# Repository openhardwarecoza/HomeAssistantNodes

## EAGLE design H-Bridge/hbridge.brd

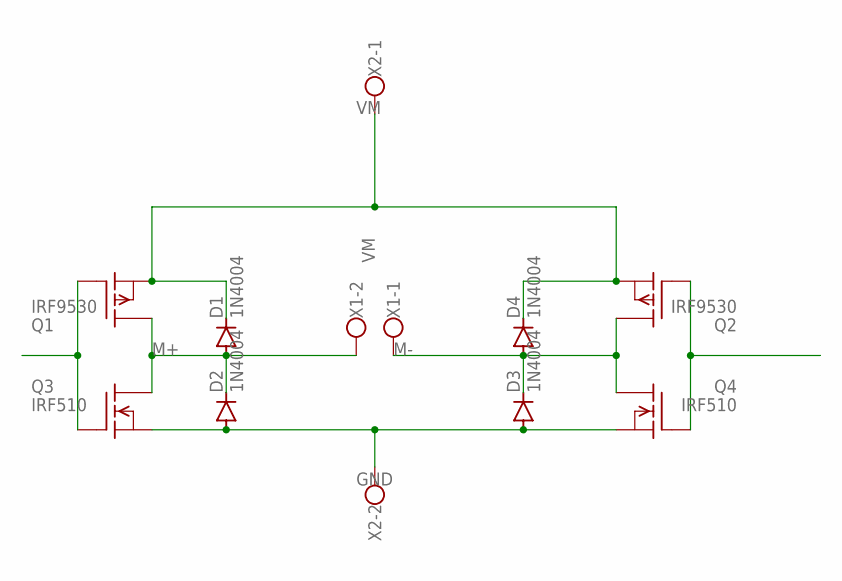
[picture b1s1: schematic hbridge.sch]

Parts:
D1, D2, D3, D4: 1N4004; DO41-10
Q1, Q2: IRF9530; TO220
Q3, Q4: IRF510; TO220
X1, X2: W237-102

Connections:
GND: D2.A, D3.A, Q3.3 (S), Q4.3 (S), X2.2
M+: D1.A, D2.C, Q1.2 (D), Q3.2 (D), X1.2
M-: D3.C, D4.A, Q2.2 (D), Q4.2 (D), X1.1
unnamed: Q1.1 (G), Q3.1 (G)
unnamed: Q2.1 (G), Q4.1 (G)
VM: D1.C, D4.C, Q1.3 (S), Q2.3 (S), X2.1

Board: 2 copper layers, 10 parts (0 on the bottom side), 6 nets, no tracks yet.

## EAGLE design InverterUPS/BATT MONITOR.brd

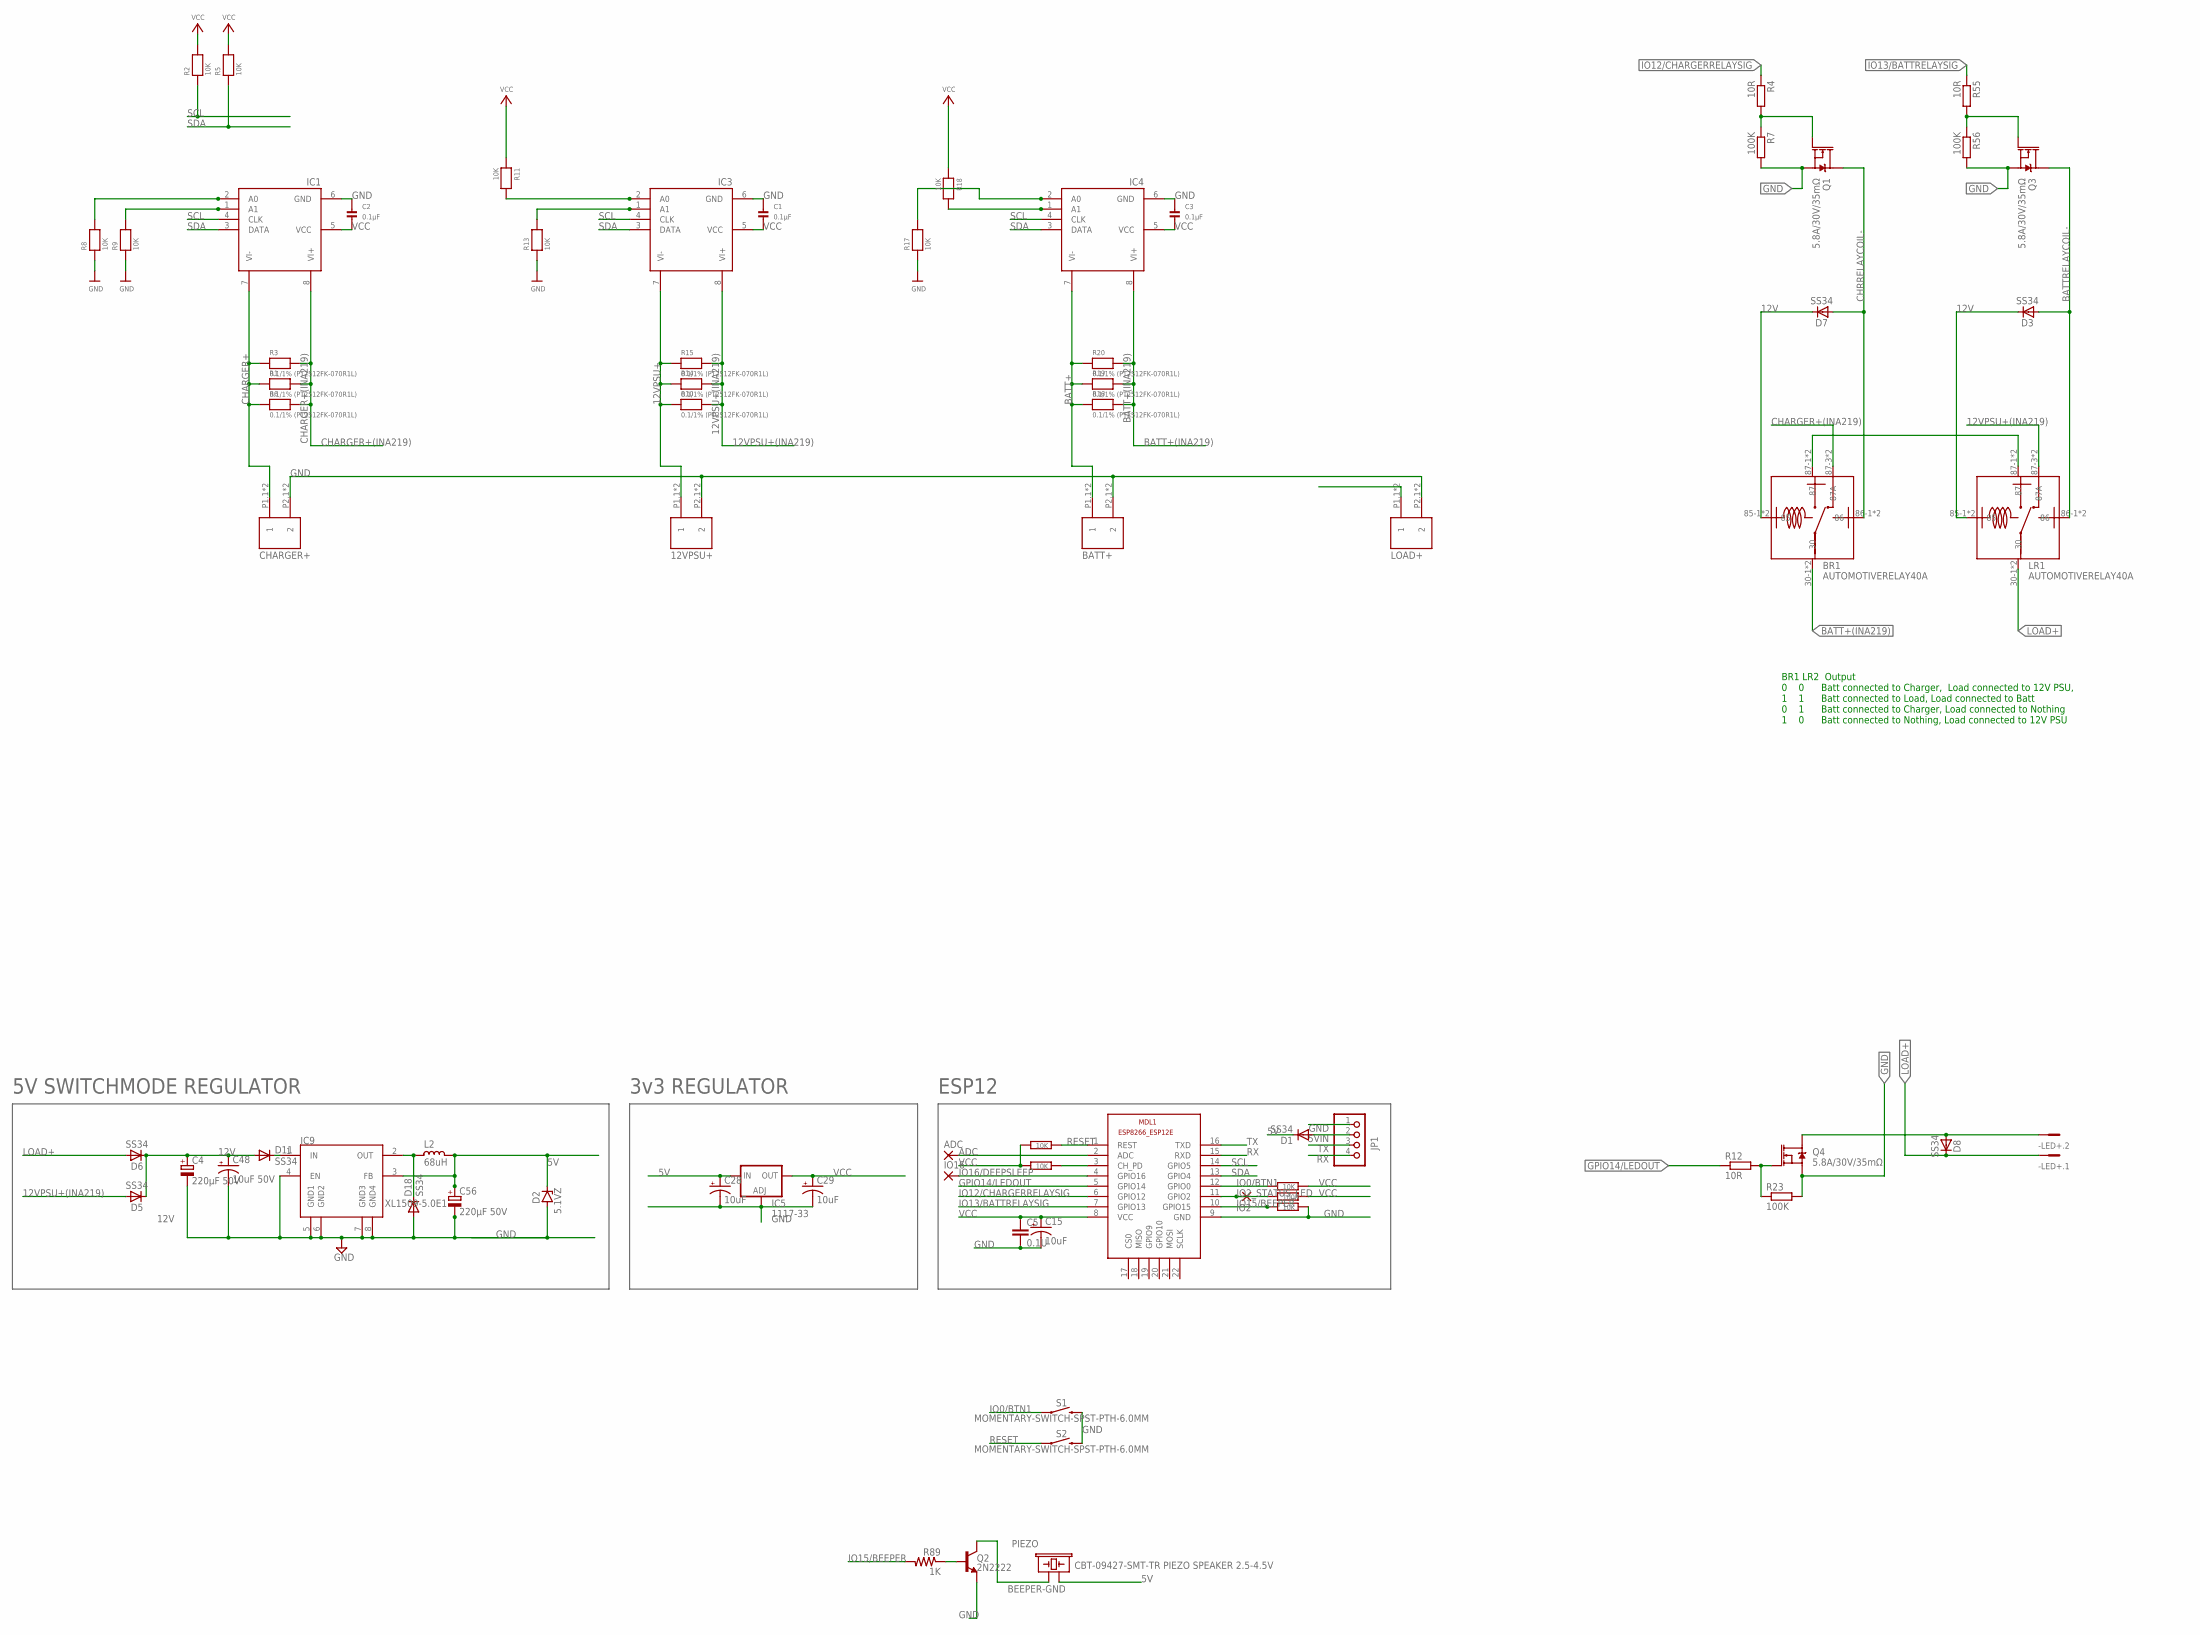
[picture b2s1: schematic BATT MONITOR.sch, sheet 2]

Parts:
-LED+: MCV2
ADC: 2,54/1,1
BR1: AUTOMOTIVERELAY40A
C1, C2, C3: 0.1µF; 1206
C4, C56: 220µF 50V; E3,5-10
C5: 0.1U; C1206
C15, C28, C29: 10uF; EIA3216
C48: 10uF 50V; EIA3216
CHARGER1, CHARGER2, CHARGER3, CHARGER4: BARRIERTERMINAL
D1, D11, D18: SS34; DO-214AC
D2: 5.1VZ; SMB
D3, D5, D6, D7, D8: SS34; SOD87
IC1, IC3, IC4: INA219D; SO08
IC5: 1117-33; SOT223
IC9: XL1509-5.0E1; SO08
IO2, IO16: 2,54/1,1
JP1: PINHD-1X4; 1X04
L2: 68uH; CD75
LR1: AUTOMOTIVERELAY40A
MDL1: ESP8266-12EESP8266-ESP12E; ESP8266-ESP12E
PIEZO: CBT-09427-SMT-TR PIEZO SPEAKER 2.5-4.5V; BUZZER-12MM
Q1, Q3, Q4: 5.8A/30V/35mΩ; SOT23-3
Q2: 2N2222; SOT23-3
R1, R3, R6, R10, R14, R15, R16, R19, R20: 0.1/1% (PT2512FK-070R1L); 2512
R2, R5, R8, R9, R11, R13, R17, R18: 10K; 1206
R4, R55: 10R; R1206
R7, R21, R56: 100K; R1206
R12: 10R; M1206
R22, R28, R29, R31: 10K; R1206
R23: 100K; M1206
R89: 1K; R1206
S1, S2: MOMENTARY-SWITCH-SPST-PTH-6.0MM; TACTILE_SWITCH_PTH_6.0MM

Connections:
5V: C28.A (+), C56.+, D1.1 (C), D2.C, IC5.3 (IN), IC9.3 (FB), L2.1, PIEZO.+ (1)
5VIN: D1.2 (A), JP1.2
12V: BR1.85-1 (85), BR1.85-2 (85), C4.+, C48.A (+), D3.1 (C), D5.1 (C), D6.1 (C), D7.1 (C), D11.2 (A), LR1.85-1 (85), LR1.85-2 (85)
12VPSU+: CHARGER4.P1.1 (1), CHARGER4.P1.2 (1), IC3.7 (VI-), R10.1, R14.1, R15.1
12VPSU+(INA219): D5.2 (A), IC3.8 (VI+), LR1.87-3 (87A), LR1.87-4 (87A), R10.2, R14.2, R15.2
ADC: ADC.1, MDL1.2 (ADC)
BATT+: CHARGER1.P1.1 (1), CHARGER1.P1.2 (1), IC4.7 (VI-), R16.1, R19.1, R20.1
BATT+(INA219): BR1.30-1 (30), BR1.30-2 (30), IC4.8 (VI+), R16.2, R19.2, R20.2
BATTRELAYCOIL-: D3.2 (A), LR1.86-1 (86), LR1.86-2 (86), Q3.3 (D)
BEEPER-GND: PIEZO.- (2), Q2.3 (C)
CHARGER+: CHARGER3.P1.1 (1), CHARGER3.P1.2 (1), IC1.7 (VI-), R1.1, R3.1, R6.1
CHARGER+(INA219): BR1.87-3 (87A), BR1.87-4 (87A), IC1.8 (VI+), R1.2, R3.2, R6.2
CHRRELAYCOIL-: BR1.86-1 (86), BR1.86-2 (86), D7.2 (A), Q1.3 (D)
GND: C1.1, C2.1, C3.1, C4.-, C5.2, C15.C (-), C28.C (-), C29.C (-), C48.C (-), C56.-, CHARGER1.P2.1 (2), CHARGER1.P2.2 (2), CHARGER2.P2.1 (2), CHARGER2.P2.2 (2), CHARGER3.P2.1 (2), CHARGER3.P2.2 (2), CHARGER4.P2.1 (2), CHARGER4.P2.2 (2), D2.A, D18.2 (A), IC1.6 (GND), IC3.6 (GND), IC4.6 (GND), IC5.1 (ADJ), IC9.4 (EN), IC9.5 (GND1), IC9.6 (GND2), IC9.7 (GND3), IC9.8 (GND4), JP1.1, MDL1.9 (GND), Q1.2 (S), Q2.2 (E), Q3.2 (S), Q4.2 (S), R7.2, R8.1, R9.1, R13.1, R17.1, R23.2, R31.2, R56.2, S1.3 (2), S2.3 (2)
GPIO14/LEDOUT: MDL1.5 (GPIO14), R12.1
IO0/BTN1: MDL1.12 (GPIO0), R22.1, S1.1
IO2_STATUS_LED: IO2.1, MDL1.11 (GPIO2), R21.1
IO12/CHARGERRELAYSIG: MDL1.6 (GPIO12), R4.1
IO13/BATTRELAYSIG: MDL1.7 (GPIO13), R55.1
IO15/BEEPER: MDL1.10 (GPIO15), R31.1, R89.2
IO16/DEEPSLEEP: IO16.1, MDL1.4 (GPIO16)
LOAD+: -LED+.1, CHARGER2.P1.1 (1), CHARGER2.P1.2 (1), D6.2 (A), D8.1 (C), LR1.30-1 (30), LR1.30-2 (30)
unnamed: D18.1 (C), IC9.2 (OUT), L2.2
unnamed: Q4.1 (G), R12.2, R23.1
unnamed: IC1.1 (A1), R9.2
unnamed: IC1.2 (A0), R8.2
unnamed: Q1.1 (G), R4.2, R7.1
unnamed: BR1.87-1 (87), BR1.87-2 (87), LR1.87-1 (87), LR1.87-2 (87)
unnamed: Q2.1 (B), R89.1
unnamed: IC3.1 (A1), R13.2
unnamed: IC3.2 (A0), R11.2
unnamed: IC4.1 (A1), R18.2
unnamed: IC4.2 (A0), R17.2
unnamed: MDL1.3 (CH_PD), R28.2
unnamed: D11.1 (C), IC9.1 (IN)
unnamed: Q3.1 (G), R55.2, R56.1
unnamed: -LED+.2, D8.2 (A), Q4.3 (D)
RESET: MDL1.1 (REST), R29.2, S2.1
RX: JP1.4, MDL1.15 (RXD)
SCL: IC1.4 (CLK), IC3.4 (CLK), IC4.4 (CLK), MDL1.14 (GPIO5), R2.1
SDA: IC1.3 (DATA), IC3.3 (DATA), IC4.3 (DATA), MDL1.13 (GPIO4), R5.1
TX: JP1.3, MDL1.16 (TXD)
VCC: C1.2, C2.2, C3.2, C5.1, C15.A (+), C29.A (+), IC1.5 (VCC), IC3.5 (VCC), IC4.5 (VCC), IC5.4 (OUT), MDL1.8 (VCC), R2.2, R5.2, R11.1, R18.1, R21.2, R22.2, R28.1, R29.1

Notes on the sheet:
BR1 LR2 Output 0 0 Batt connected to Charger, Load connected to 12V PSU, 1 1 Batt connected to Load, Load connected to Batt 0 1 Batt connected to Charger, Load connected to Nothing 1 0 Batt connected to Nothing, Load connected to 12V PSU
5V SWITCHMODE REGULATOR
3v3 REGULATOR
ESP12

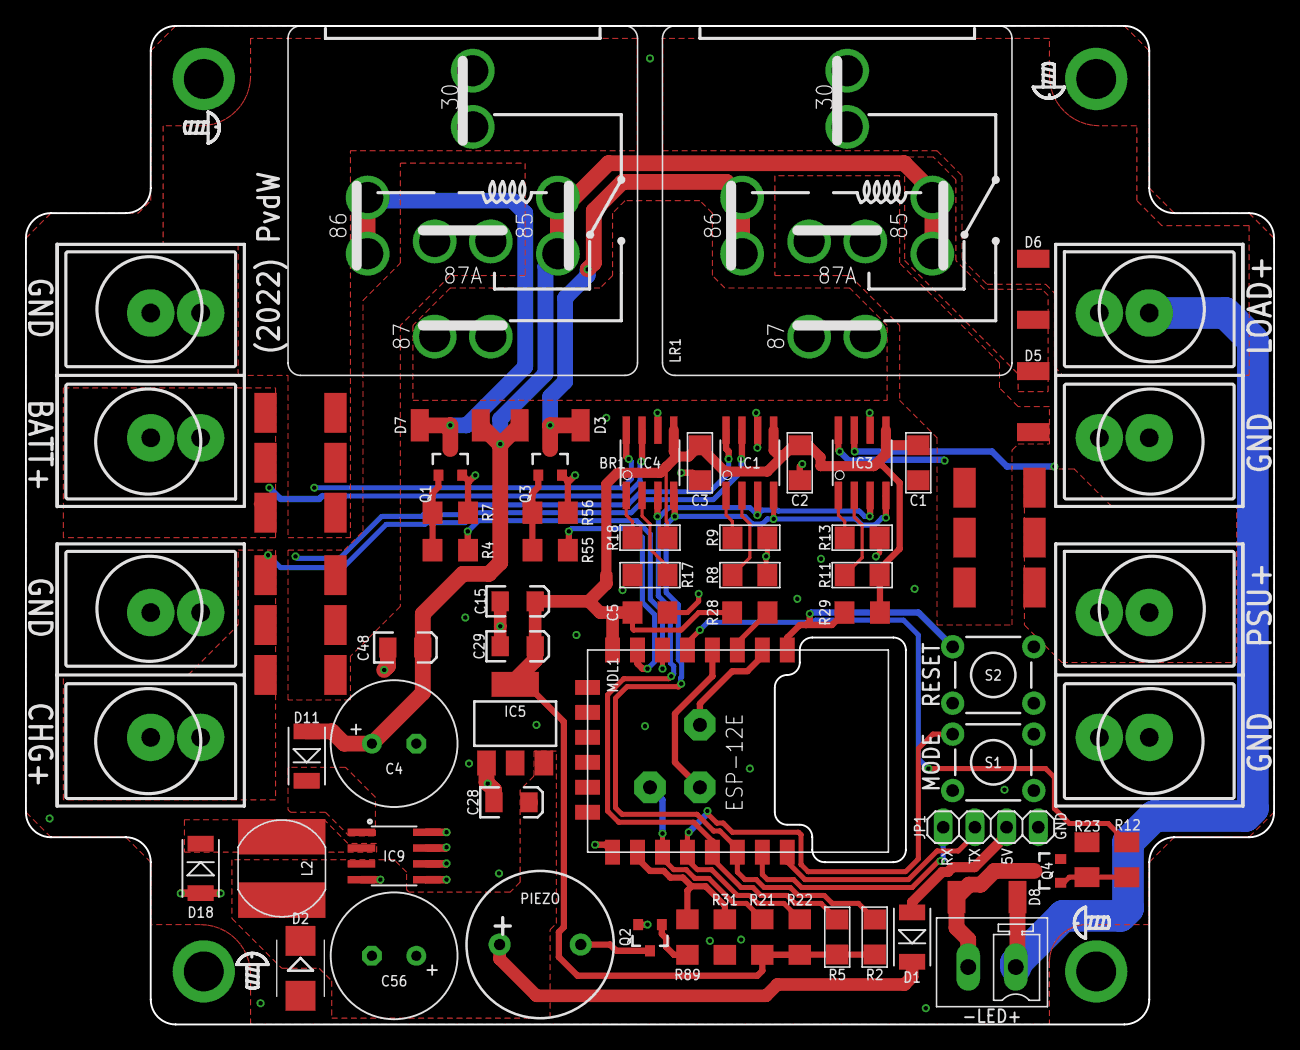
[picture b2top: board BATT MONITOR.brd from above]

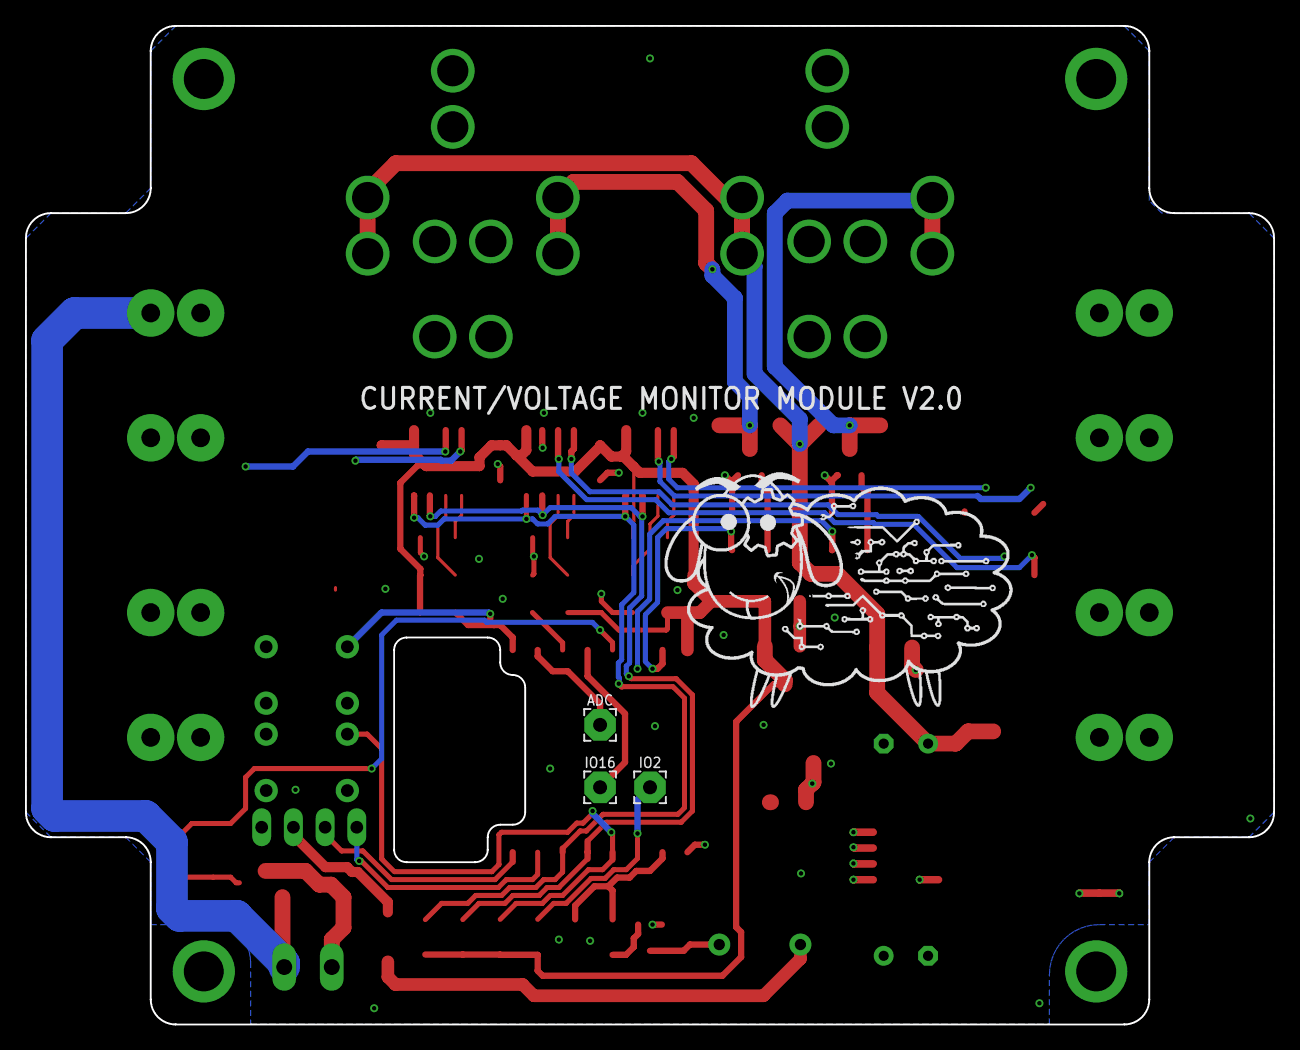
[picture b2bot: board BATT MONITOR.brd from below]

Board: 2 copper layers, 100.0 x 80.0 mm, 73 parts (3 on the bottom side), 43 nets.

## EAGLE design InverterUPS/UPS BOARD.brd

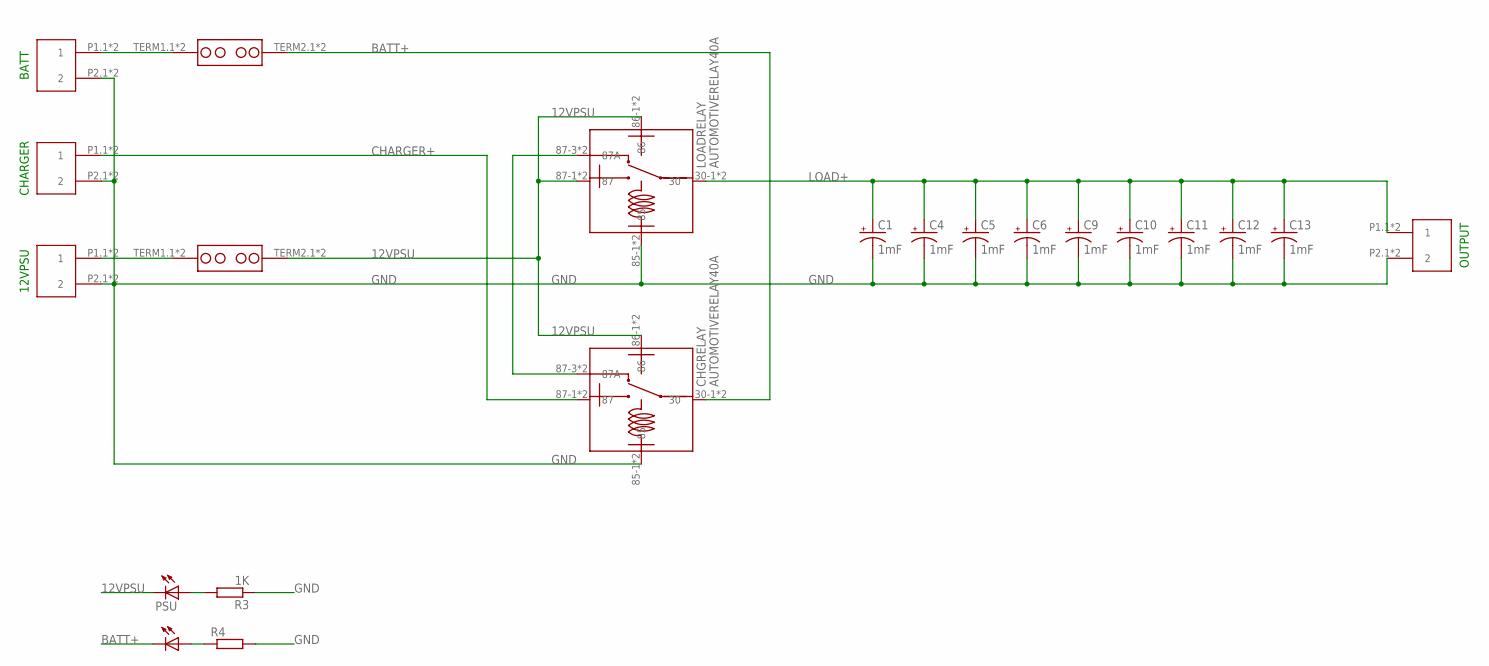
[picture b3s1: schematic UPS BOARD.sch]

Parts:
BATT: LED5MM
C1, C4, C5, C6, C9, C10, C11, C12, C13: 1mF; CPOL-RADIAL-5MM-10MM
CHARGER2, CHARGER3, CHARGER4, CHARGER5: BARRIERTERMINAL
CHGRELAY: AUTOMOTIVERELAY40A
LOADRELAY: AUTOMOTIVERELAY40A
PSU: LED5MM
R3, R4: 1K; 0204/7
U$15, U$17: ATQ-FUSE

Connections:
12VPSU: CHGRELAY.86-1 (86), CHGRELAY.86-2 (86), LOADRELAY.86-1 (86), LOADRELAY.86-2 (86), LOADRELAY.87-1 (87), LOADRELAY.87-2 (87), PSU.K (C), U$17.TERM2.1, U$17.TERM2.2
BATT+: BATT.K (C), CHGRELAY.30-1 (30), CHGRELAY.30-2 (30), U$15.TERM2.1, U$15.TERM2.2
CHARGER+: CHARGER5.P1.1 (1), CHARGER5.P1.2 (1), CHGRELAY.87-1 (87), CHGRELAY.87-2 (87)
GND: C1.-, C4.-, C5.-, C6.-, C9.-, C10.-, C11.-, C12.-, C13.-, CHARGER2.P2.1 (2), CHARGER2.P2.2 (2), CHARGER3.P2.1 (2), CHARGER3.P2.2 (2), CHARGER4.P2.1 (2), CHARGER4.P2.2 (2), CHARGER5.P2.1 (2), CHARGER5.P2.2 (2), CHGRELAY.85-1 (85), CHGRELAY.85-2 (85), LOADRELAY.85-1 (85), LOADRELAY.85-2 (85), R3.1, R4.2
LOAD+: C1.+, C4.+, C5.+, C6.+, C9.+, C10.+, C11.+, C12.+, C13.+, CHARGER4.P1.1 (1), CHARGER4.P1.2 (1), LOADRELAY.30-1 (30), LOADRELAY.30-2 (30)
unnamed: PSU.A, R3.2
unnamed: BATT.A, R4.1
unnamed: CHARGER3.P1.1 (1), CHARGER3.P1.2 (1), U$17.TERM1.1, U$17.TERM1.2
unnamed: CHGRELAY.87-3 (87A), CHGRELAY.87-4 (87A), LOADRELAY.87-3 (87A), LOADRELAY.87-4 (87A)
unnamed: CHARGER2.P1.1 (1), CHARGER2.P1.2 (1), U$15.TERM1.1, U$15.TERM1.2

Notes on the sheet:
CHARGER
12VPSU
OUTPUT
BATT

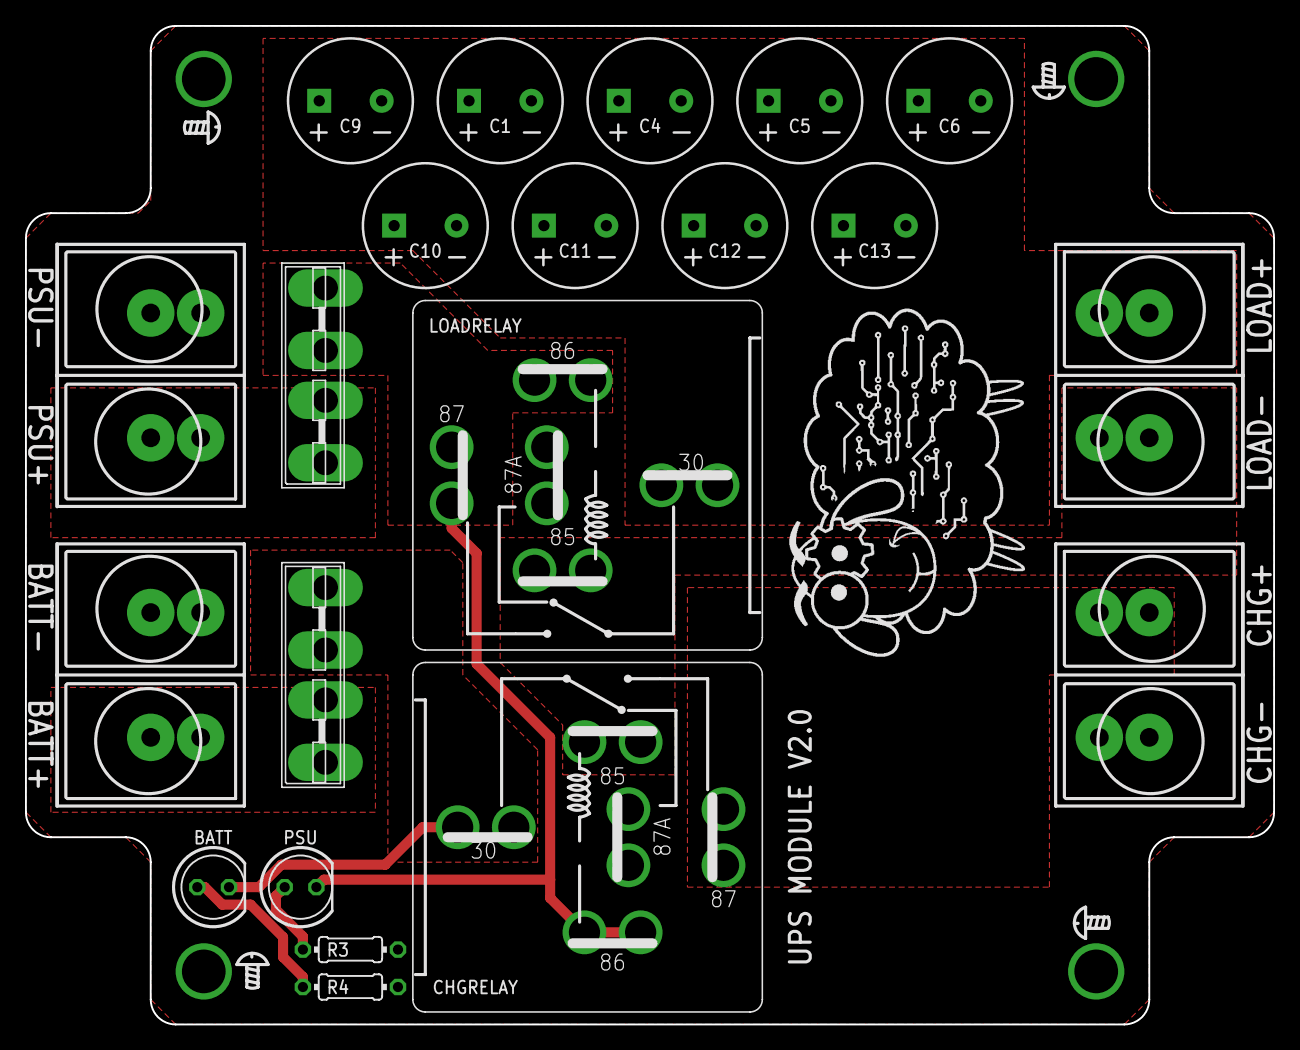
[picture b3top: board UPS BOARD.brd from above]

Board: 2 copper layers, 100.0 x 80.0 mm, 21 parts (0 on the bottom side), 10 nets.

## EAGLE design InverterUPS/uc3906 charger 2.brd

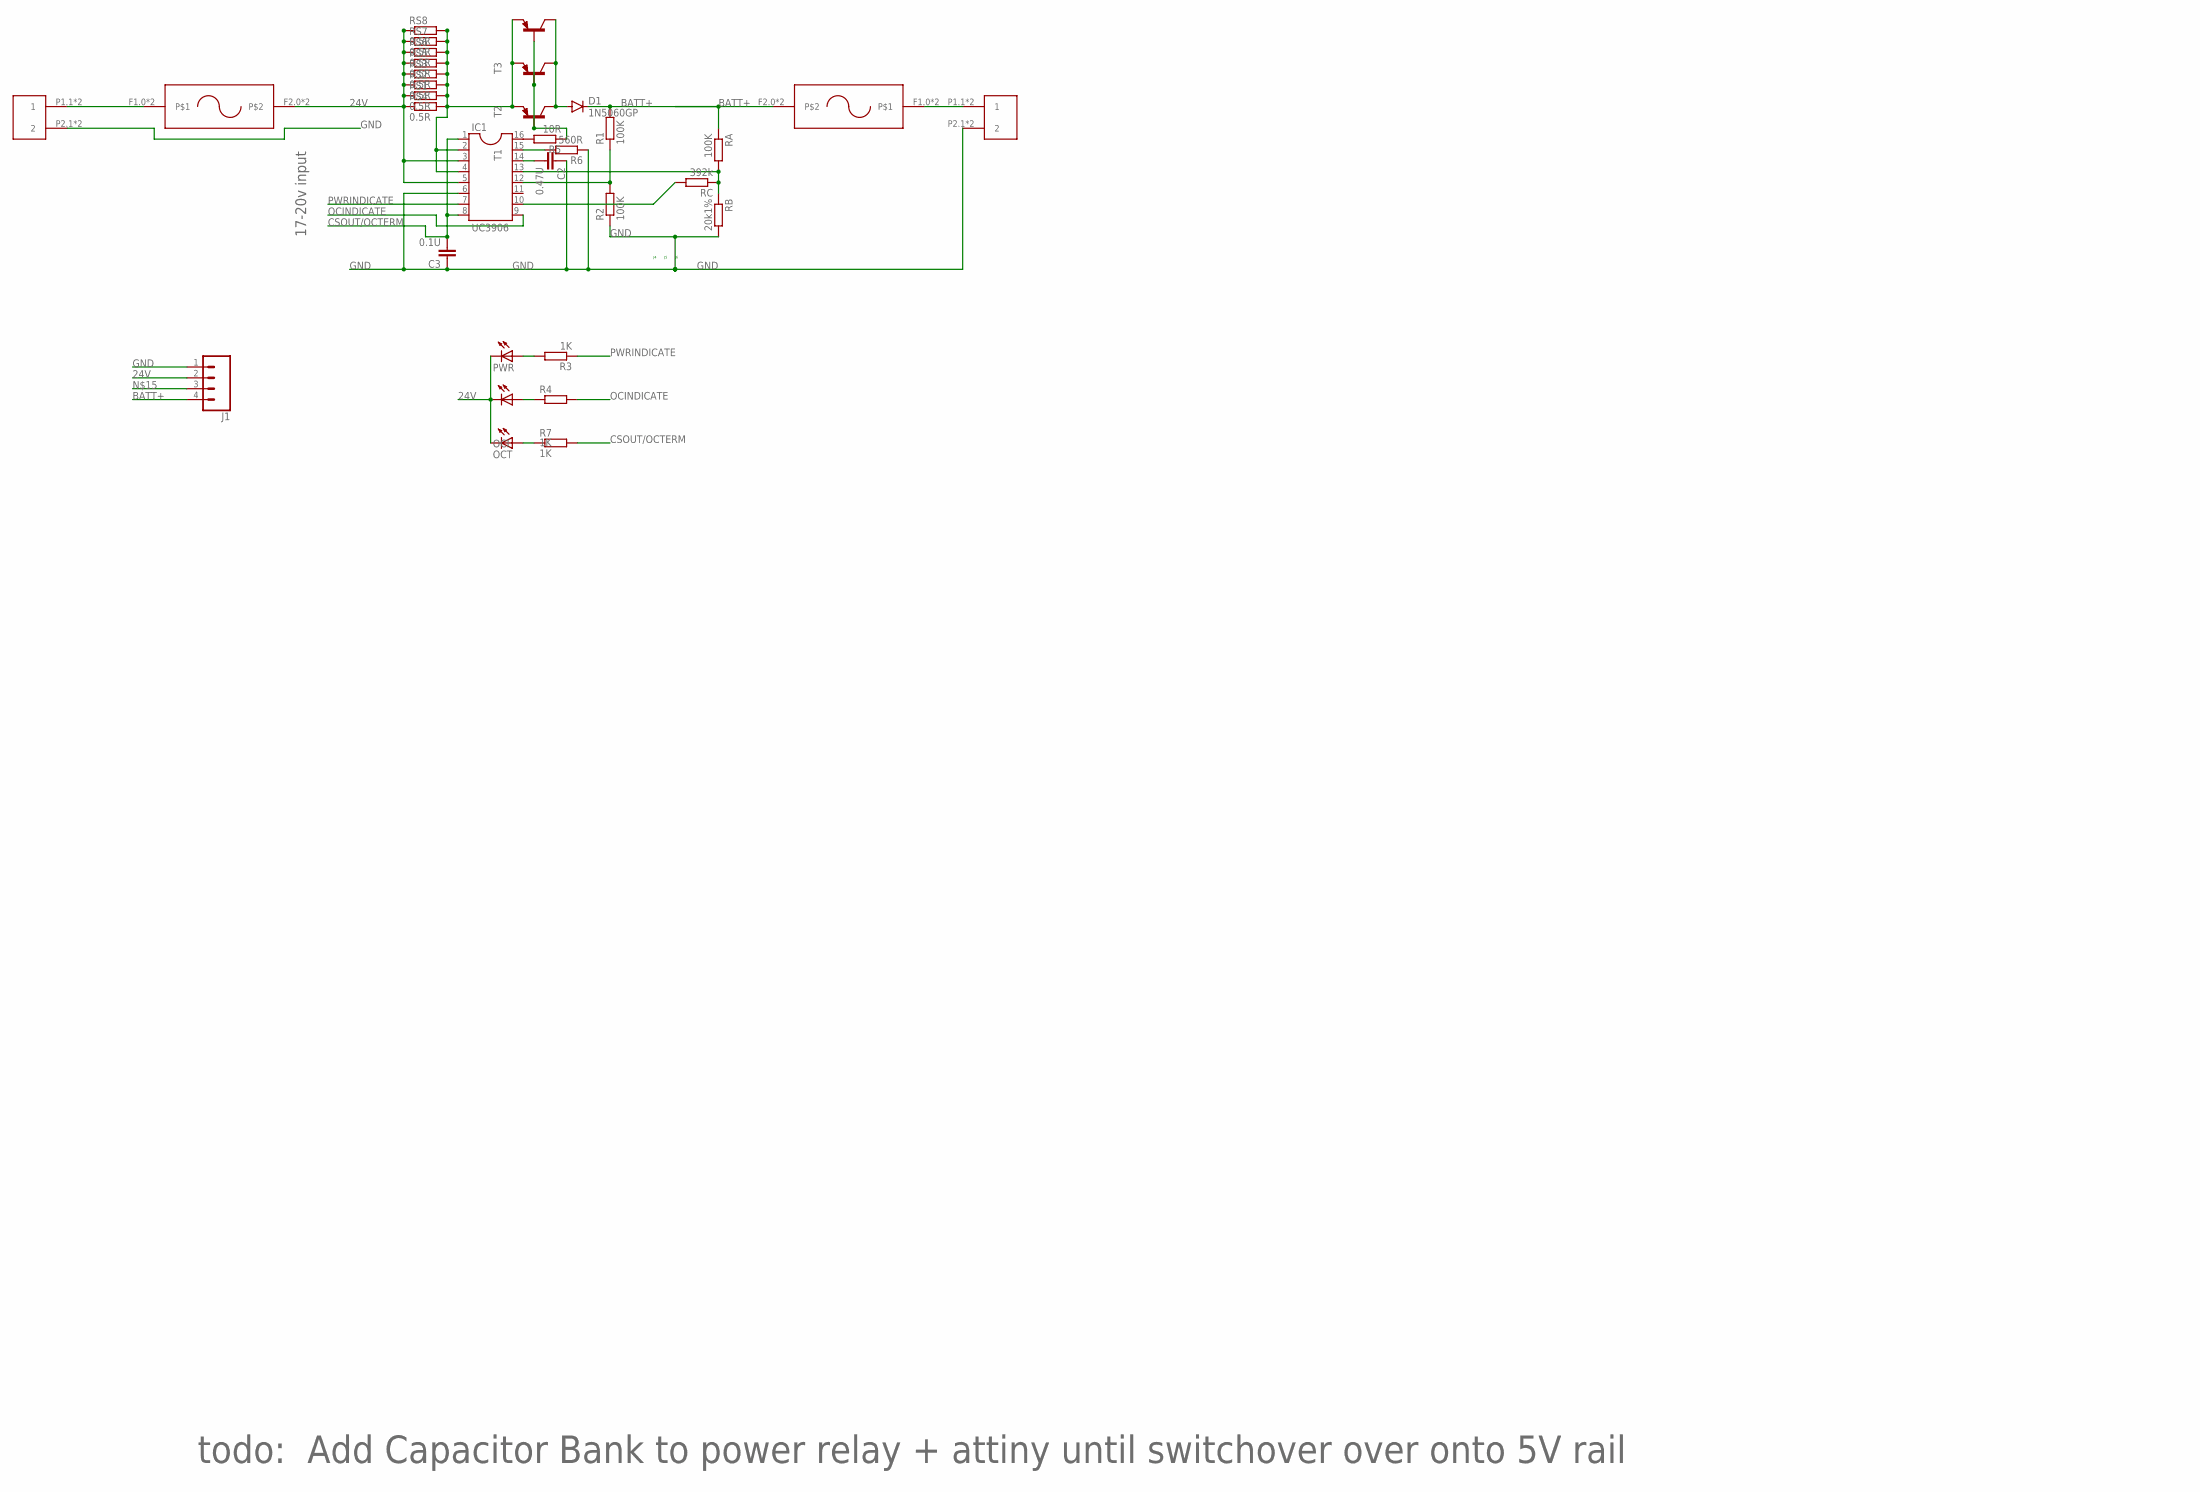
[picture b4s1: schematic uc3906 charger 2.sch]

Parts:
BATT: BARRIERTERMINAL
C2: 0.47U; C050-024X044
C3: 0.1U; C050-024X044
D1: 1N5060GP; DO15-12
IC1: UC3906; DIL16
J1: CONN_04LONGPADS; 1X04_LONGPADS
OCI: LED5MM
OCT: LED5MM
POWERIN: BARRIERTERMINAL
PWR: LED5MM
R1, R2: 100K; 0204/7
R3, R4, R7: 1K; 0204/7
R5: 10R; 0204/7
R6: 560R; 0204/7
RA: 100K; 0204/7
RB: 20k1%; 0204/7
RC: 392k; 0204/7
RS1, RS2, RS3, RS4, RS5, RS6, RS7, RS8: 0.5R; 0411/15
T1, T2, T3: TIP32C; TO220
U$1, U$2: 18MMFUSEHOLDER

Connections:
24V: IC1.3, IC1.5, J1.2, OCI.K (C), OCT.K (C), PWR.K (C), RS1.1, RS2.1, RS3.1, RS4.1, RS5.1, RS6.1, RS7.1, RS8.1, U$2.F2.0, U$2.F2.1
BATT+: D1.C, J1.4, R1.2, RA.1, U$1.F2.0, U$1.F2.1
CHARGEENABLE: IC1.12, R1.1, R2.2
COMPENSATION: C2.2, IC1.14
CSOUT/OCTERM: C3.2, IC1.1, IC1.8, R7.2
DRIVERSINK: IC1.16, R5.2
DRIVERSOURCE: IC1.15, R6.2
GND: BATT.P2.1 (2), BATT.P2.2 (2), C2.1, C3.1, IC1.6, J1.1, POWERIN.P2.1 (2), POWERIN.P2.2 (2), R2.1, R6.1, RB.2
IOUT: IC1.2, IC1.4, RS1.2, RS2.2, RS3.2, RS4.2, RS5.2, RS6.2, RS7.2, RS8.2, T1.3 (E), T2.3 (E), T3.3 (E)
unnamed: POWERIN.P1.1 (1), POWERIN.P1.2 (1), U$2.F1.0, U$2.F1.1
unnamed: PWR.A, R3.2
unnamed: OCI.A, R4.1
unnamed: OCT.A, R7.1
unnamed: BATT.P1.1 (1), BATT.P1.2 (1), U$1.F1.0, U$1.F1.1
unnamed: R5.1, T1.1 (B), T2.1 (B), T3.1 (B)
unnamed: D1.A, J1.3, T1.2 (C), T2.2 (C), T3.2 (C)
OCINDICATE: IC1.9, R4.2
PWRINDICATE: IC1.7, R3.1
STATELEVELCONTROL: IC1.10, RC.2
VSENSE: IC1.13, RA.2, RB.1, RC.1

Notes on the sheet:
17-20v input
todo: Add Capacitor Bank to power relay + attiny until switchover over onto 5V rail

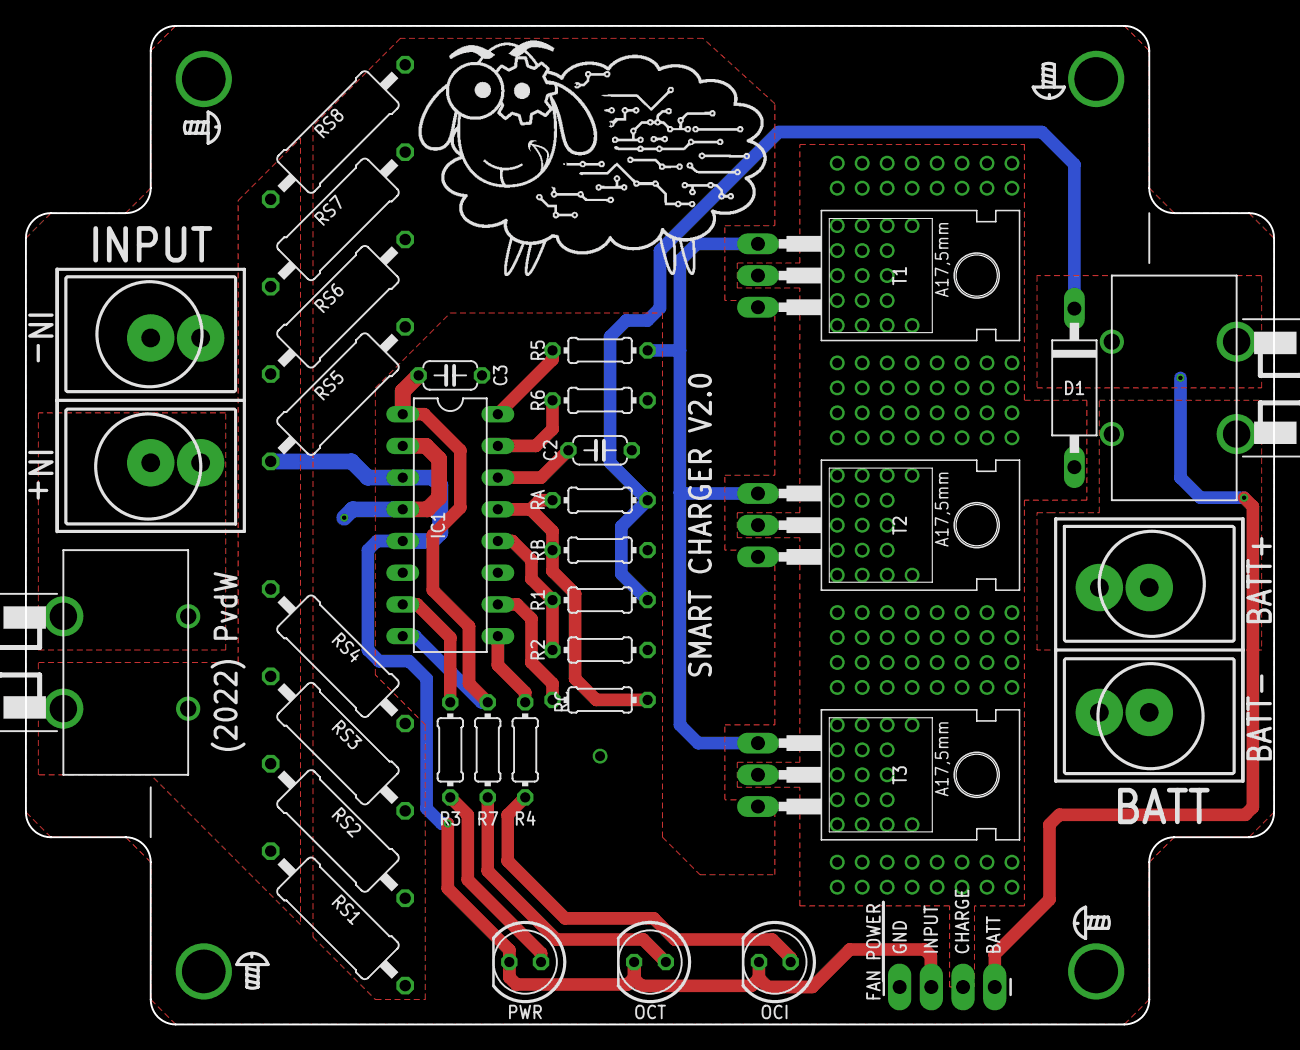
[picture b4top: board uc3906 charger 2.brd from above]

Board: 2 copper layers, 100.0 x 80.0 mm, 33 parts (0 on the bottom side), 20 nets.

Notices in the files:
parts and their libraries:
SparkFun-Electromechanical: Licensing: Creative Commons ShareAlike 4.0 International - https://creativecommons.org/licenses/by-sa/4.0
rc-master-smd: Copyright (C) 2007, Bob Starr
SparkFun-Resistors: Licensing: CC v3.0 Share-Alike You are welcome to use this library for commercial purposes.
